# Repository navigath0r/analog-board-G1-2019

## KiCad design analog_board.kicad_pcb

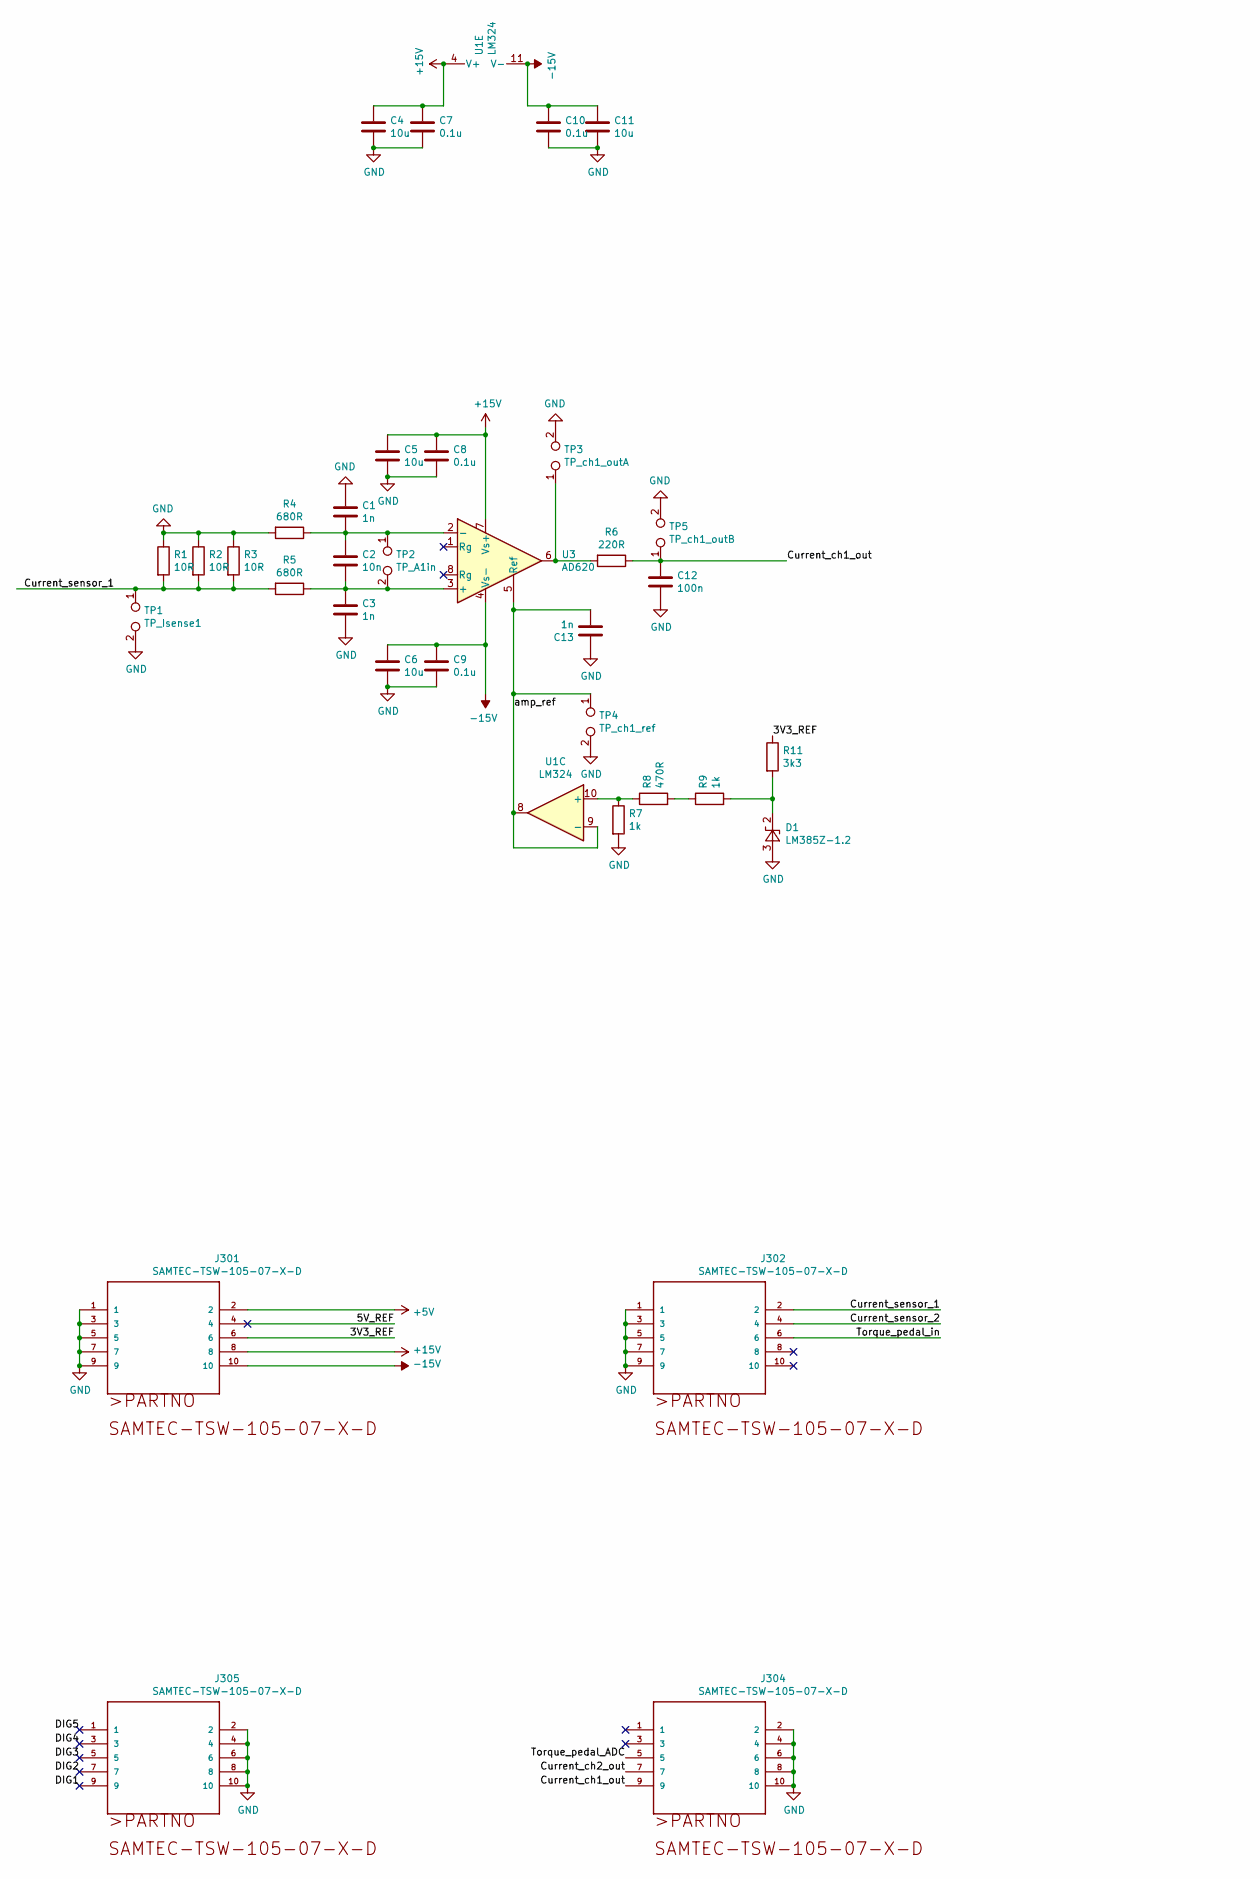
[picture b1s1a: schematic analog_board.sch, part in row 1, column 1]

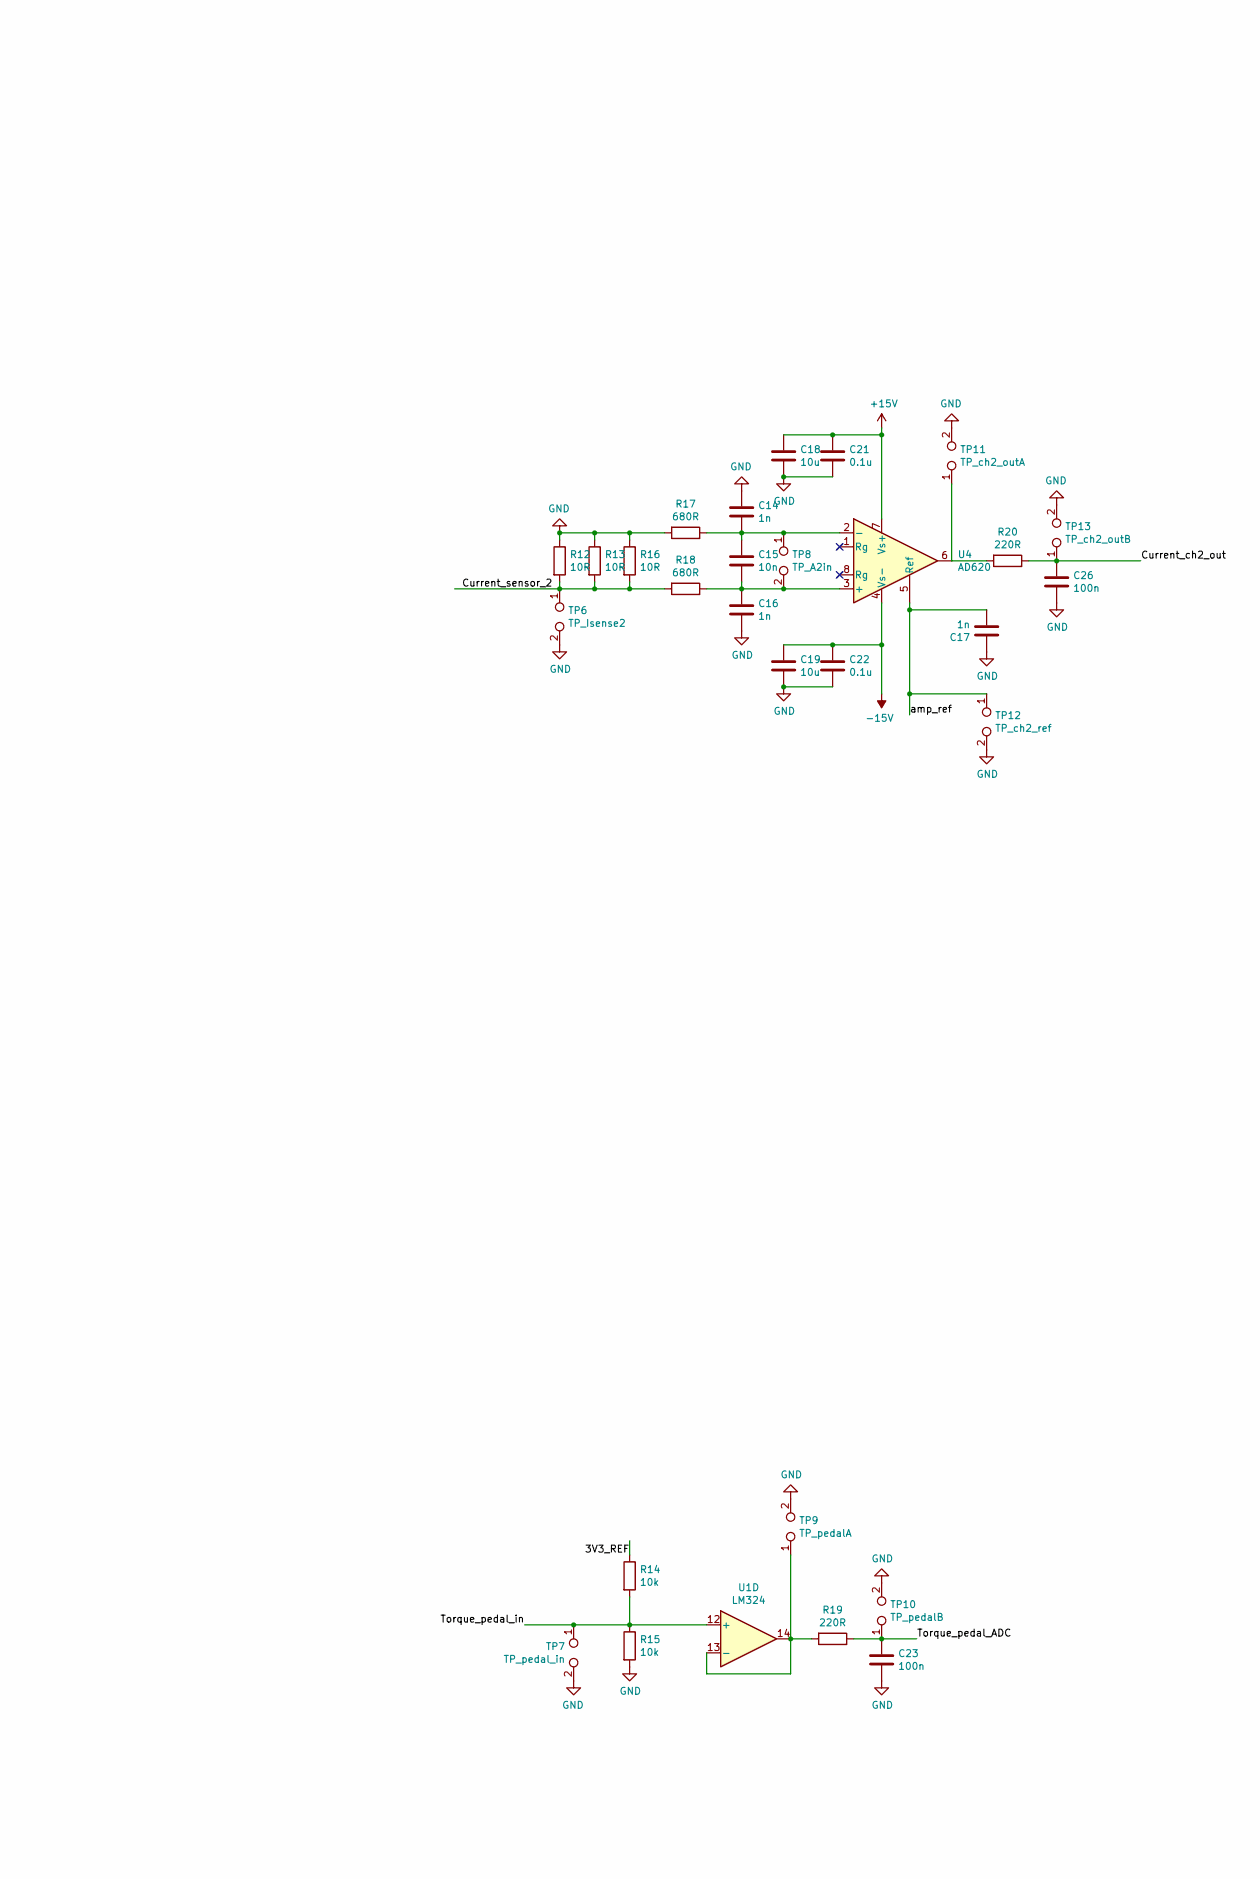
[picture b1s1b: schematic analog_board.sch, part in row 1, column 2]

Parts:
C1, C3, C13, C14, C16, C17: 1n; C_0805_2012Metric_Pad1.15x1.40mm_HandSolder
C2, C15: 10n; C_0805_2012Metric_Pad1.15x1.40mm_HandSolder
C4, C5, C6, C11, C18, C19: 10u; C_0805_2012Metric_Pad1.15x1.40mm_HandSolder
C7, C8, C9, C10, C21, C22: 0.1u; C_0805_2012Metric_Pad1.15x1.40mm_HandSolder
C12, C23, C26: 100n; C_0805_2012Metric_Pad1.15x1.40mm_HandSolder
D1: LM385Z-1.2; TO-92_Inline
J301, J302, J304, J305: SAMTEC-TSW-105-07-X-D; PinSocket_2x05_P2.54mm_Vertical
R1, R2, R3, R12, R13, R16: 10R; R_0805_2012Metric_Pad1.15x1.40mm_HandSolder
R4, R5, R17, R18: 680R; R_0805_2012Metric_Pad1.15x1.40mm_HandSolder
R6, R19, R20: 220R; R_0805_2012Metric_Pad1.15x1.40mm_HandSolder
R7, R9: 1k; R_0805_2012Metric_Pad1.15x1.40mm_HandSolder
R8: 470R; R_0805_2012Metric_Pad1.15x1.40mm_HandSolder
R11: 3k3; R_0805_2012Metric_Pad1.15x1.40mm_HandSolder
R14, R15: 10k; R_0805_2012Metric_Pad1.15x1.40mm_HandSolder
TP1: TP_Isense1; TestPoint_2Pads_Pitch2.54mm_Drill0.8mm
TP2: TP_A1in; TestPoint_2Pads_Pitch2.54mm_Drill0.8mm
TP3: TP_ch1_outA; TestPoint_2Pads_Pitch2.54mm_Drill0.8mm
TP4: TP_ch1_ref; TestPoint_2Pads_Pitch2.54mm_Drill0.8mm
TP5: TP_ch1_outB; TestPoint_2Pads_Pitch2.54mm_Drill0.8mm
TP6: TP_Isense2; TestPoint_2Pads_Pitch2.54mm_Drill0.8mm
TP7: TP_pedal_in; TestPoint_2Pads_Pitch2.54mm_Drill0.8mm
TP8: TP_A2in; TestPoint_2Pads_Pitch2.54mm_Drill0.8mm
TP9: TP_pedalA; TestPoint_2Pads_Pitch2.54mm_Drill0.8mm
TP10: TP_pedalB; TestPoint_2Pads_Pitch2.54mm_Drill0.8mm
TP11: TP_ch2_outA; TestPoint_2Pads_Pitch2.54mm_Drill0.8mm
TP12: TP_ch2_ref; TestPoint_2Pads_Pitch2.54mm_Drill0.8mm
TP13: TP_ch2_outB; TestPoint_2Pads_Pitch2.54mm_Drill0.8mm
U1: LM324; DIP-14_W7.62mm
U3, U4: AD620; DIP-8_W7.62mm

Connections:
+5V: J301.2
+15V: C4.1, C5.1, C7.1, C8.1, C18.1, C21.1, J301.8, U1.4 (V+), U3.7 (Vs+), U4.7 (Vs+)
-15V: C6.1, C9.1, C10.1, C11.1, C19.1, C22.1, J301.10, U1.11 (V-), U3.4 (Vs-), U4.4 (Vs-)
/3V3_REF: J301.6, R11.1, R14.1
/5V_REF: J301.4
/Current_ch1_out: C12.1, J304.9, R6.1, TP5.1
/Current_ch2_out: C26.1, J304.7, R20.1, TP13.1
/Current_sensor_1: J302.2, R1.2, R2.2, R3.2, R5.2, TP1.1
/Current_sensor_2: J302.4, R12.2, R13.2, R16.2, R18.2, TP6.1
/DIG1: J305.9
/DIG2: J305.7
/DIG3: J305.5
/DIG4: J305.3
/DIG5: J305.1
/Torque_pedal_ADC: C23.1, J304.5, R19.1, TP10.1
/Torque_pedal_in: J302.6, R14.2, R15.1, TP7.1, U1.12 (+)
/amp_ref: C13.2, C17.2, TP4.1, TP12.1, U1.8, U1.9 (-), U3.5 (Ref), U4.5 (Ref)
GND: C1.1, C3.2, C4.2, C5.2, C6.2, C7.2, C8.2, C9.2, C10.2, C11.2, C12.2, C13.1, C14.1, C16.2, C17.1, C18.2, C19.2, C21.2, C22.2, C23.2, C26.2, D1.3 (A), J301.1, J301.3, J301.5, J301.7, J301.9, J302.1, J302.3, J302.5, J302.7, J302.9, J304.2, J304.4, J304.6, J304.8, J304.10, J305.2, J305.4, J305.6, J305.8, J305.10, R1.1, R2.1, R3.1, R4.2, R7.2, R12.1, R13.1, R15.2, R16.1, R17.2, TP1.2, TP3.2, TP4.2, TP5.2, TP6.2, TP7.2, TP9.2, TP10.2, TP11.2, TP12.2, TP13.2
unnamed: C1.2, C2.1, R4.1, TP2.1, U3.2 (-)
unnamed: C2.2, C3.1, R5.1, TP2.2, U3.3 (+)
unnamed: C14.2, C15.1, R17.1, TP8.1, U4.2 (-)
unnamed: C15.2, C16.1, R18.1, TP8.2, U4.3 (+)
unnamed: D1.2 (K), R9.2, R11.2
unnamed: R6.2, TP3.1, U3.6
unnamed: R7.1, R8.1, U1.10 (+)
unnamed: R8.2, R9.1
unnamed: R19.2, TP9.1, U1.13 (-), U1.14
unnamed: R20.2, TP11.1, U4.6

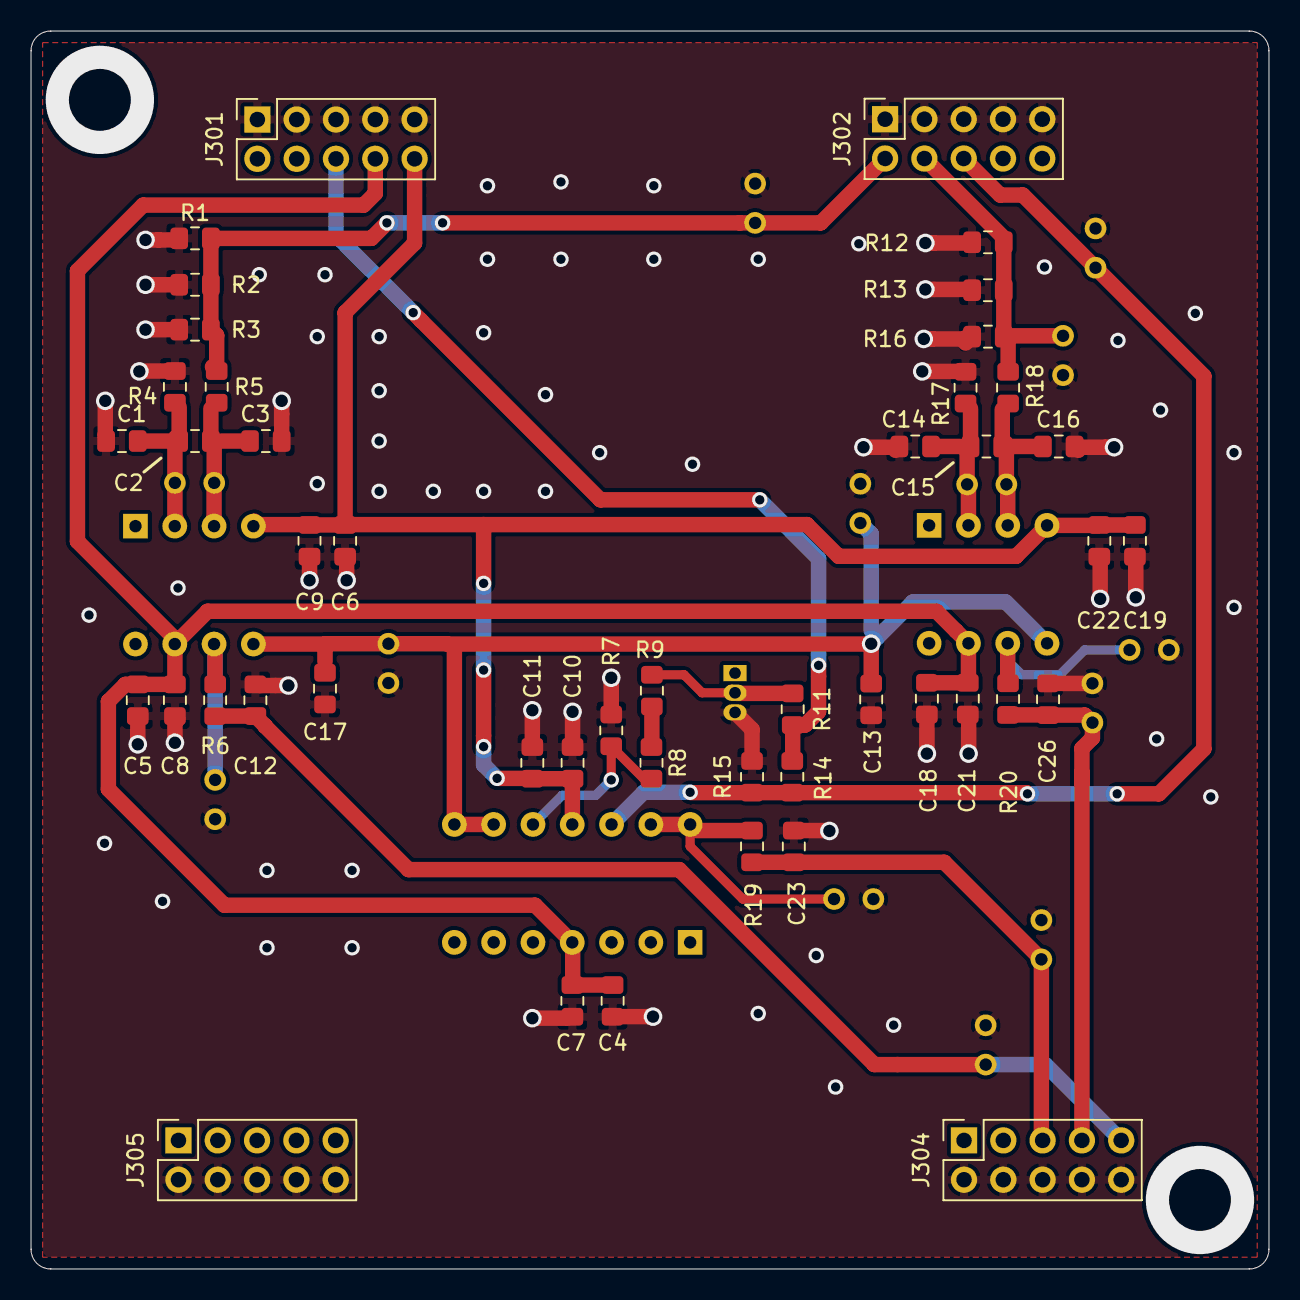
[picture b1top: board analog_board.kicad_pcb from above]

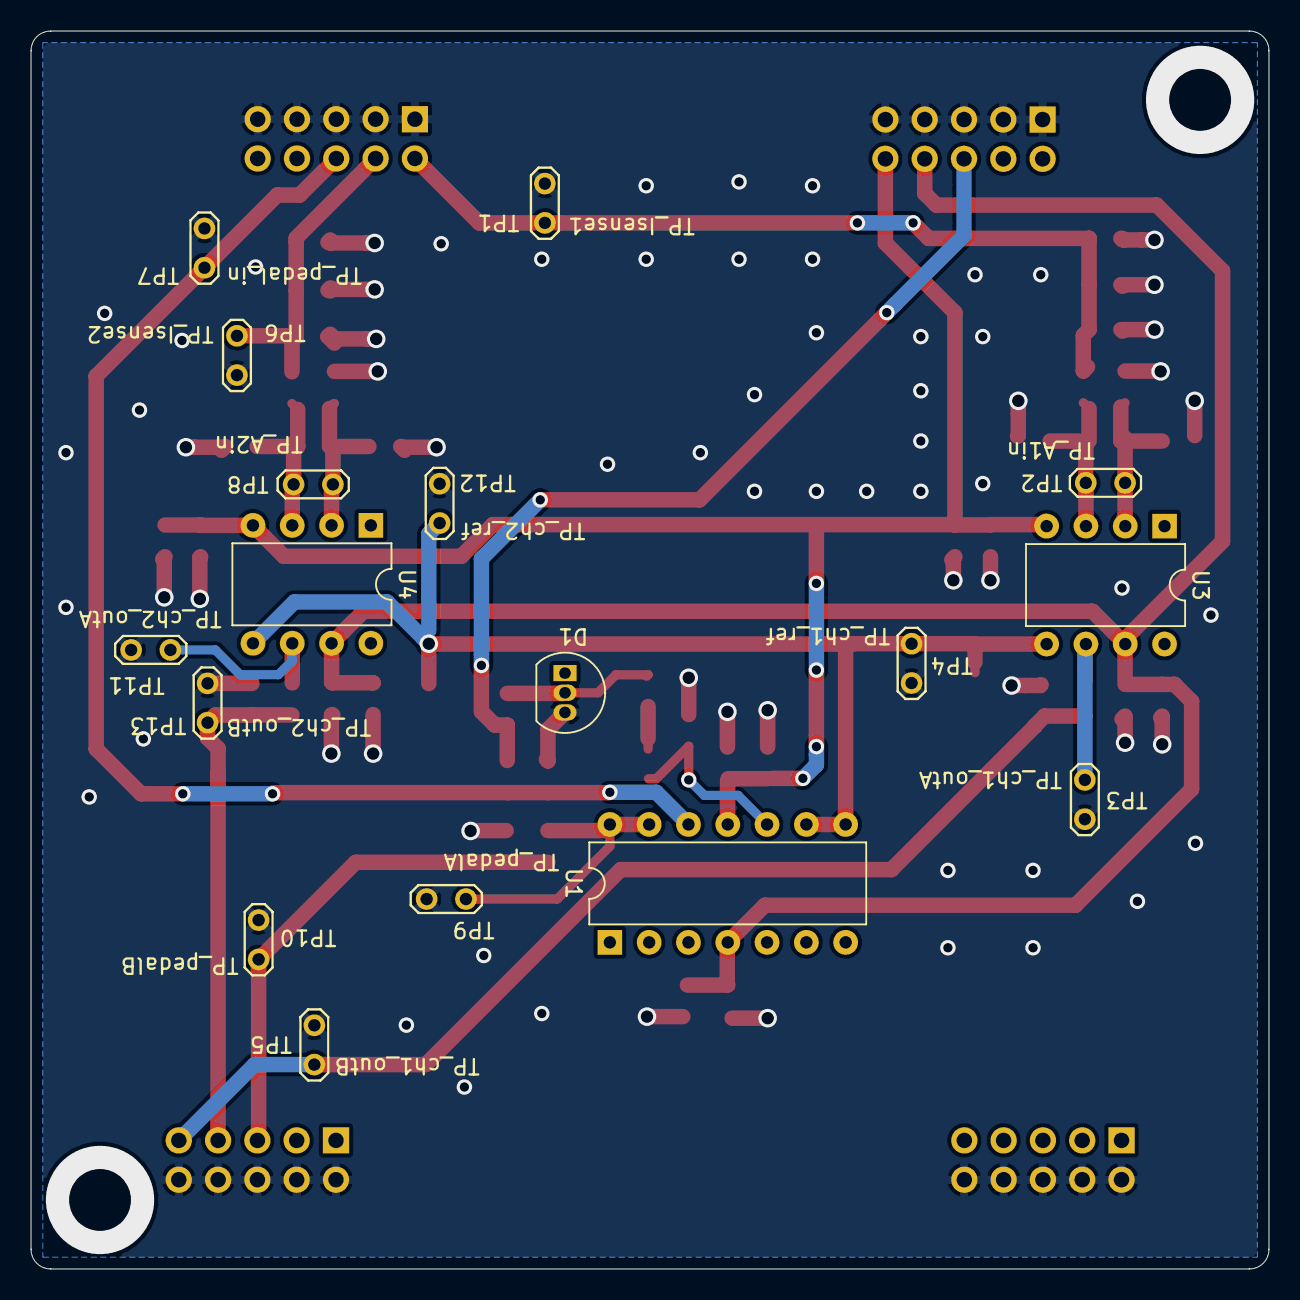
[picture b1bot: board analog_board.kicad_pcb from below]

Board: 2 copper layers, 80.0 x 80.0 mm, 63 parts (17 on the bottom side), 21 nets.

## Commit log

2019-02-14 First commit to set up the repo and see how KiCad saves
2019-02-21 Current measurement channels and connectors added
2019-02-22 Current measurement input filters, torque pedal reading
2019-02-27 Added output filters and fixed reference opamp
2019-02-27 Fixed opamp parts to the corresponding package
2019-02-27 Some footprints added, removed unnecessary REF opamps
2019-02-27 Mapped AIB-to-MB connector pins, assigned footprints
2019-02-27 Begun layout
2019-02-28 Removed te reference amp of current_ch2, layed out components No wiring yet.
2019-02-28 Most wiring is done, no ground yet
2019-03-01 All wiring done, except for grounding
2019-03-01 All wiring done, awaiting review
2019-03-04 Removed OR jumers. Realigned connectors. Moved large components to Bottom. Thickened tracks.
2019-03-05 Added test points and ground fill on top
